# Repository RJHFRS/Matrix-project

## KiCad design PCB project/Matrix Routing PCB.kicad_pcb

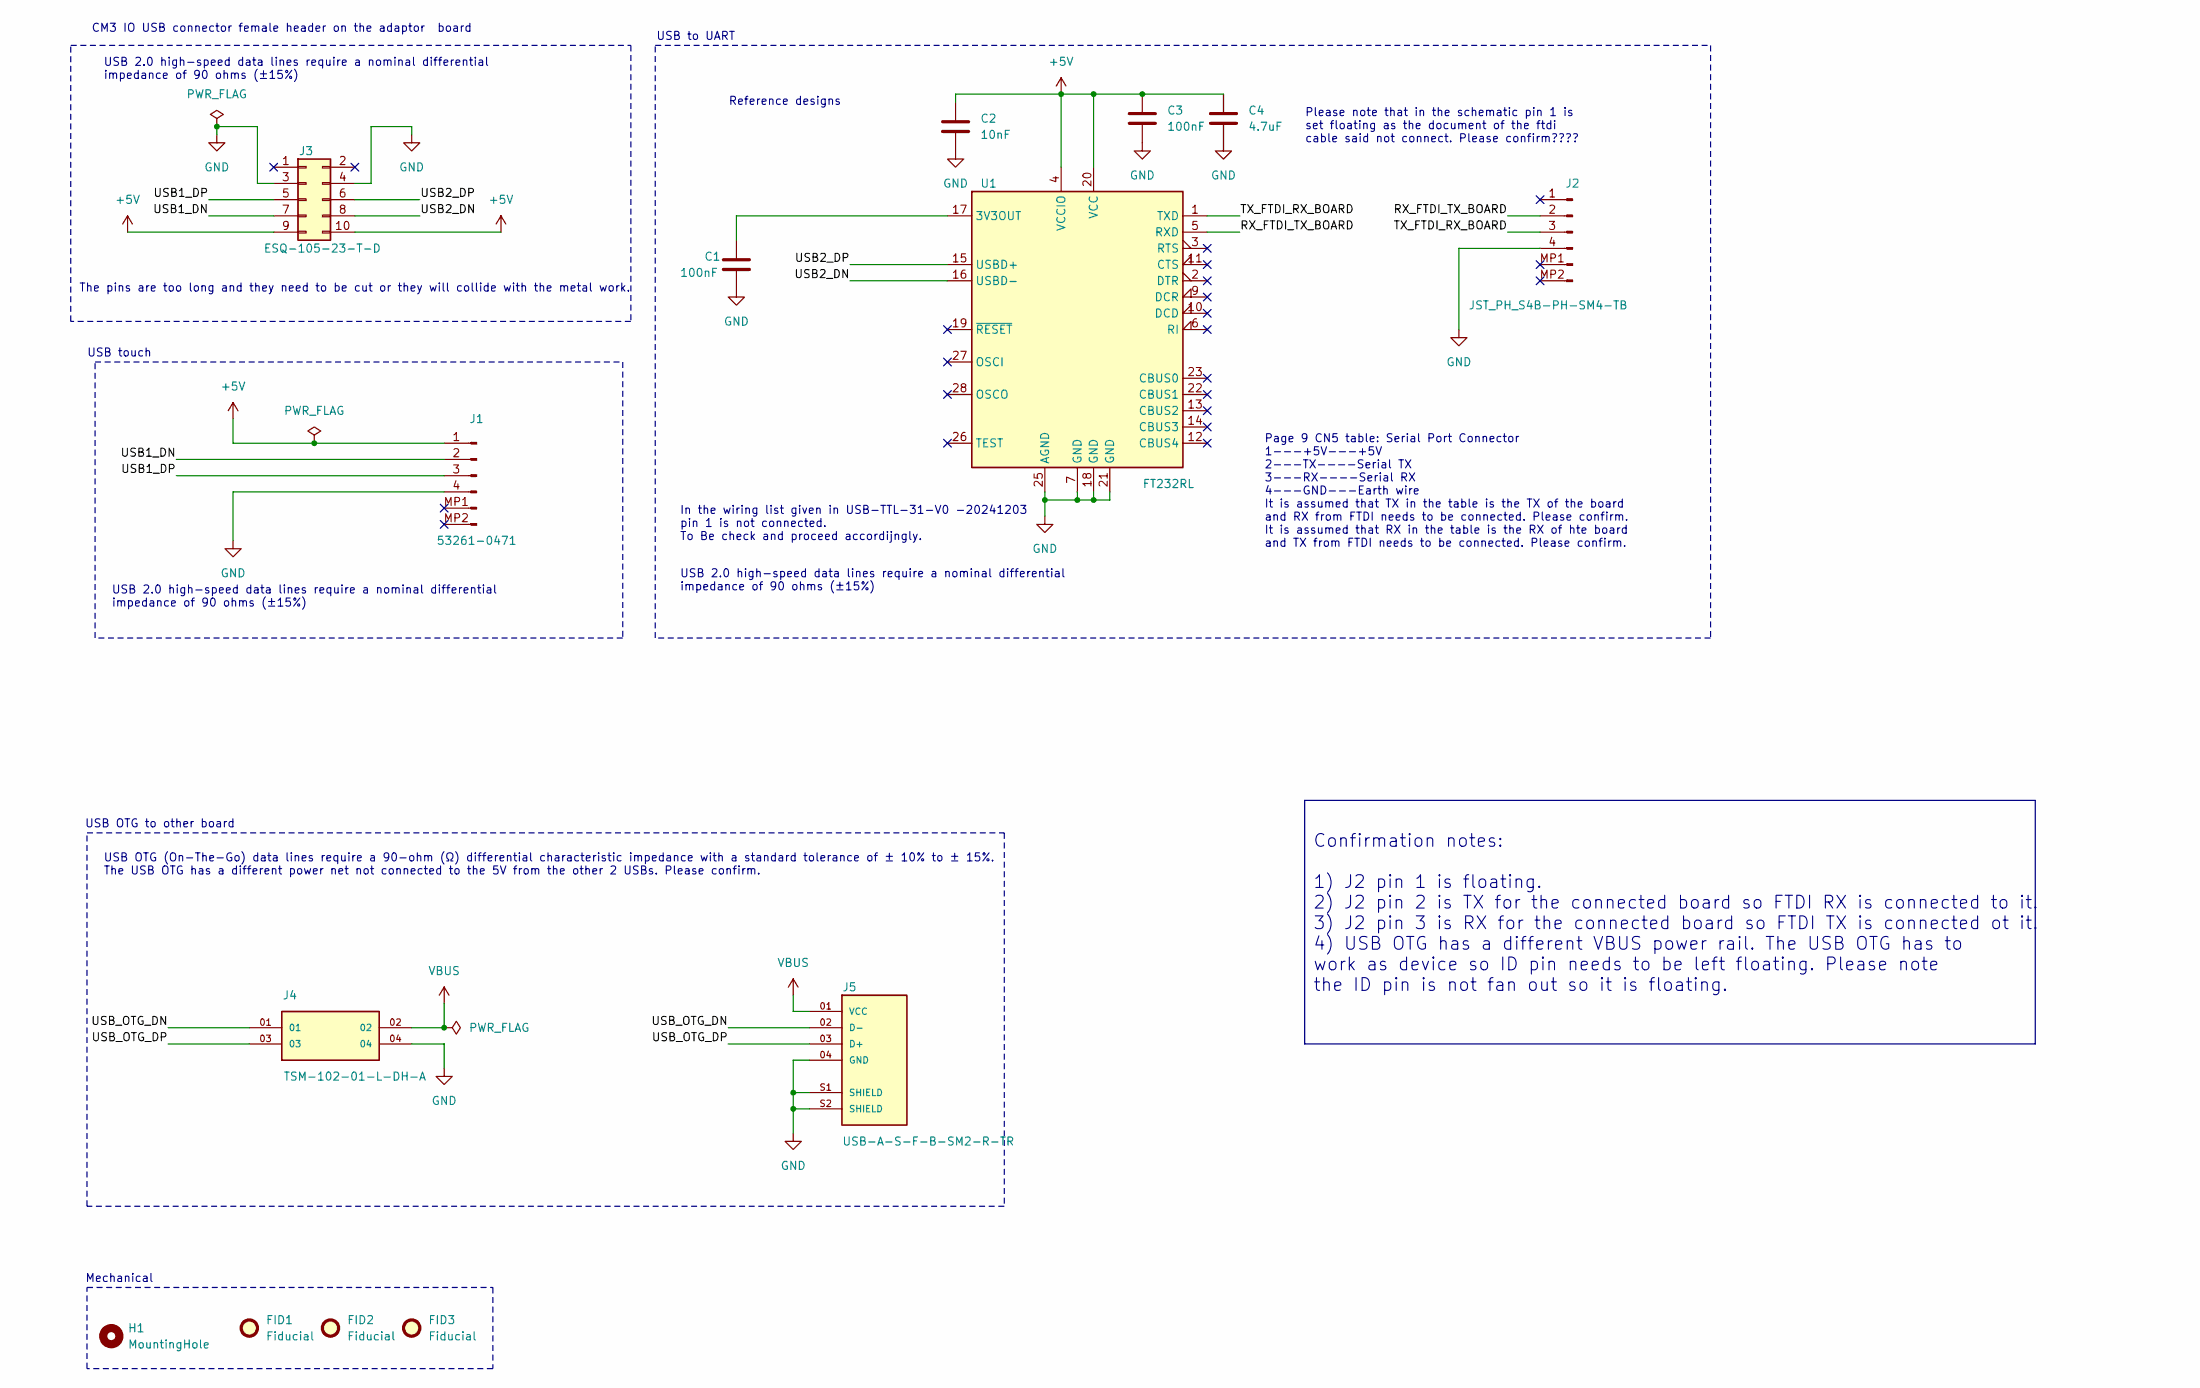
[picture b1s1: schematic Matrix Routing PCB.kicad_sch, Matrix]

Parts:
C1, C3: 100nF; C_0603_1608Metric; MPN C0603C104K4RACTU; Digikey PN 399-C0603C104K4RACTUCT-ND
C2: 10nF; C_0603_1608Metric; MPN C0603C103K5RACTU; Digikey PN 399-C0603C103K5RACTUCT-ND
C4: 4.7uF; C_0603_1608Metric; MPN GRM188C71C475KE21D; Digikey PN 490-16337-1-ND
FID1, FID2, FID3: Fiducial; Fiducial_0.5mm_Mask1.5mm
H1: MountingHole; MountingHole_3.2mm_M3
J1: 53261-0471; Molex_PicoBlade_53261-0471_1x04-1MP_P1.25mm_Horizontal; MPN 53261-0471; Digikey PN WM7622CT-ND
J2: JST_PH_S4B-PH-SM4-TB; JST_PH_S4B-PH-SM4-TB_1x04-1MP_P2.00mm_Horizontal; MPN S4B-PH-SM4-TB; Digikey PN 455-S4B-PH-SM4-TBCT-ND
J3: ESQ-105-23-T-D; ESQ-105-XX-X-D; MPN ESQ-105-33-T-D; Digikey PN ESQ-105-23-T-D-ND
J4: TSM-102-01-L-DH-A; SAMTEC_TSM-102-01-L-DH-A; PARTREV R; Digikey PN SAM15344-ND
J5: USB-A-S-F-B-SM2-R-TR; SAMTEC_USB-A-S-X-X-SM2-R; PARTREV T; Digikey PN 612-USB-A-S-F-B-SM2-R-TRCT-ND
U1: FT232RL; SSOP-28_5.3x10.2mm_P0.65mm; MPN FT232RL; Digikey PN 768-1306-ND

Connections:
+5V: C2.1, C3.1, C4.1, J1.1, J3.9, J3.10, U1.4 (VCCIO), U1.20 (VCC)
/RX_FTDI_TX_BOARD: J2.2, U1.5 (RXD)
/TX_FTDI_RX_BOARD: J2.3, U1.1 (TXD)
/USB1_DN: J1.2, J3.7
/USB1_DP: J1.3, J3.5
/USB2_DN: J3.8, U1.16 (USBD-)
/USB2_DP: J3.6, U1.15 (USBD+)
/USB_OTG_DN: J4.01, J5.02 (D-)
/USB_OTG_DP: J4.03, J5.03 (D+)
GND: C1.2, C2.2, C3.2, C4.2, J1.4, J2.4, J3.3, J3.4, J4.04, J5.04 (GND), J5.S1 (SHIELD), J5.S2 (SHIELD), U1.7 (GND), U1.18 (GND), U1.21 (GND), U1.25 (AGND)
unnamed: C1.1, U1.17 (3V3OUT)
VBUS: J4.02, J5.01 (VCC)

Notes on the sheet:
USB OTG to other board
USB to UART
The pins are too long and they need to be cut or they will collide with the metal work.
Reference designs
Confirmation notes: 1) J2 pin 1 is floating. 2) J2 pin 2 is TX for the connected board so FTDI RX is connected to it. 3) J2 pin 3 is RX for the connected board so FTDI TX is connected ot it. 4) USB OTG has a different VBUS power rail. The USB OTG has to work as device so ID pin needs to be left flo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
USB touch
Page 9 CN5 table: Serial Port Connector 1---+5V---+5V 2---TX----Serial TX 3---RX----Serial RX 4---GND---Earth wire It is assumed that TX in the table is the TX of the board and RX from FTDI needs to be connected. Please confirm. It is assumed that RX in the table is the RX of hte board and TX from 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
In the wiring list given in USB-TTL-31-V0 -20241203 pin 1 is not connected. To Be check and proceed accordijngly.
CM3 IO USB connector female header on the adaptor board
USB 2.0 high-speed data lines require a nominal differential impedance of 90 ohms (±15%)
Mechanical
Please note that in the schematic pin 1 is set floating as the document of the ftdi cable said not connect. Please confirm????
USB OTG (On-The-Go) data lines require a 90-ohm (Ω) differential characteristic impedance with a standard tolerance of ± 10% to ± 15%. The USB OTG has a different power net not connected to the 5V from the other 2 USBs. Please confirm.

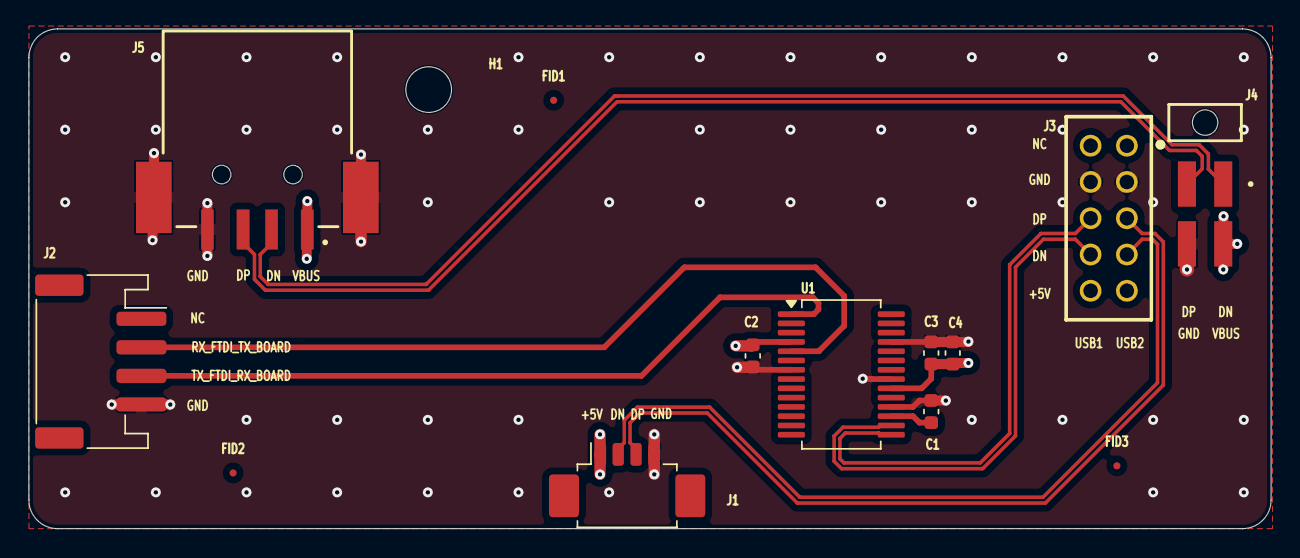
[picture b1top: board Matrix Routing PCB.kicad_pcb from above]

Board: 4 copper layers, 87.0 x 35.0 mm, 14 parts (0 on the bottom side), 12 nets.
